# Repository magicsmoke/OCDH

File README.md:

View this project on [CADLAB.io](https://cadlab.io/project/25315). 

# OCDH
Open Source Diesel Heater

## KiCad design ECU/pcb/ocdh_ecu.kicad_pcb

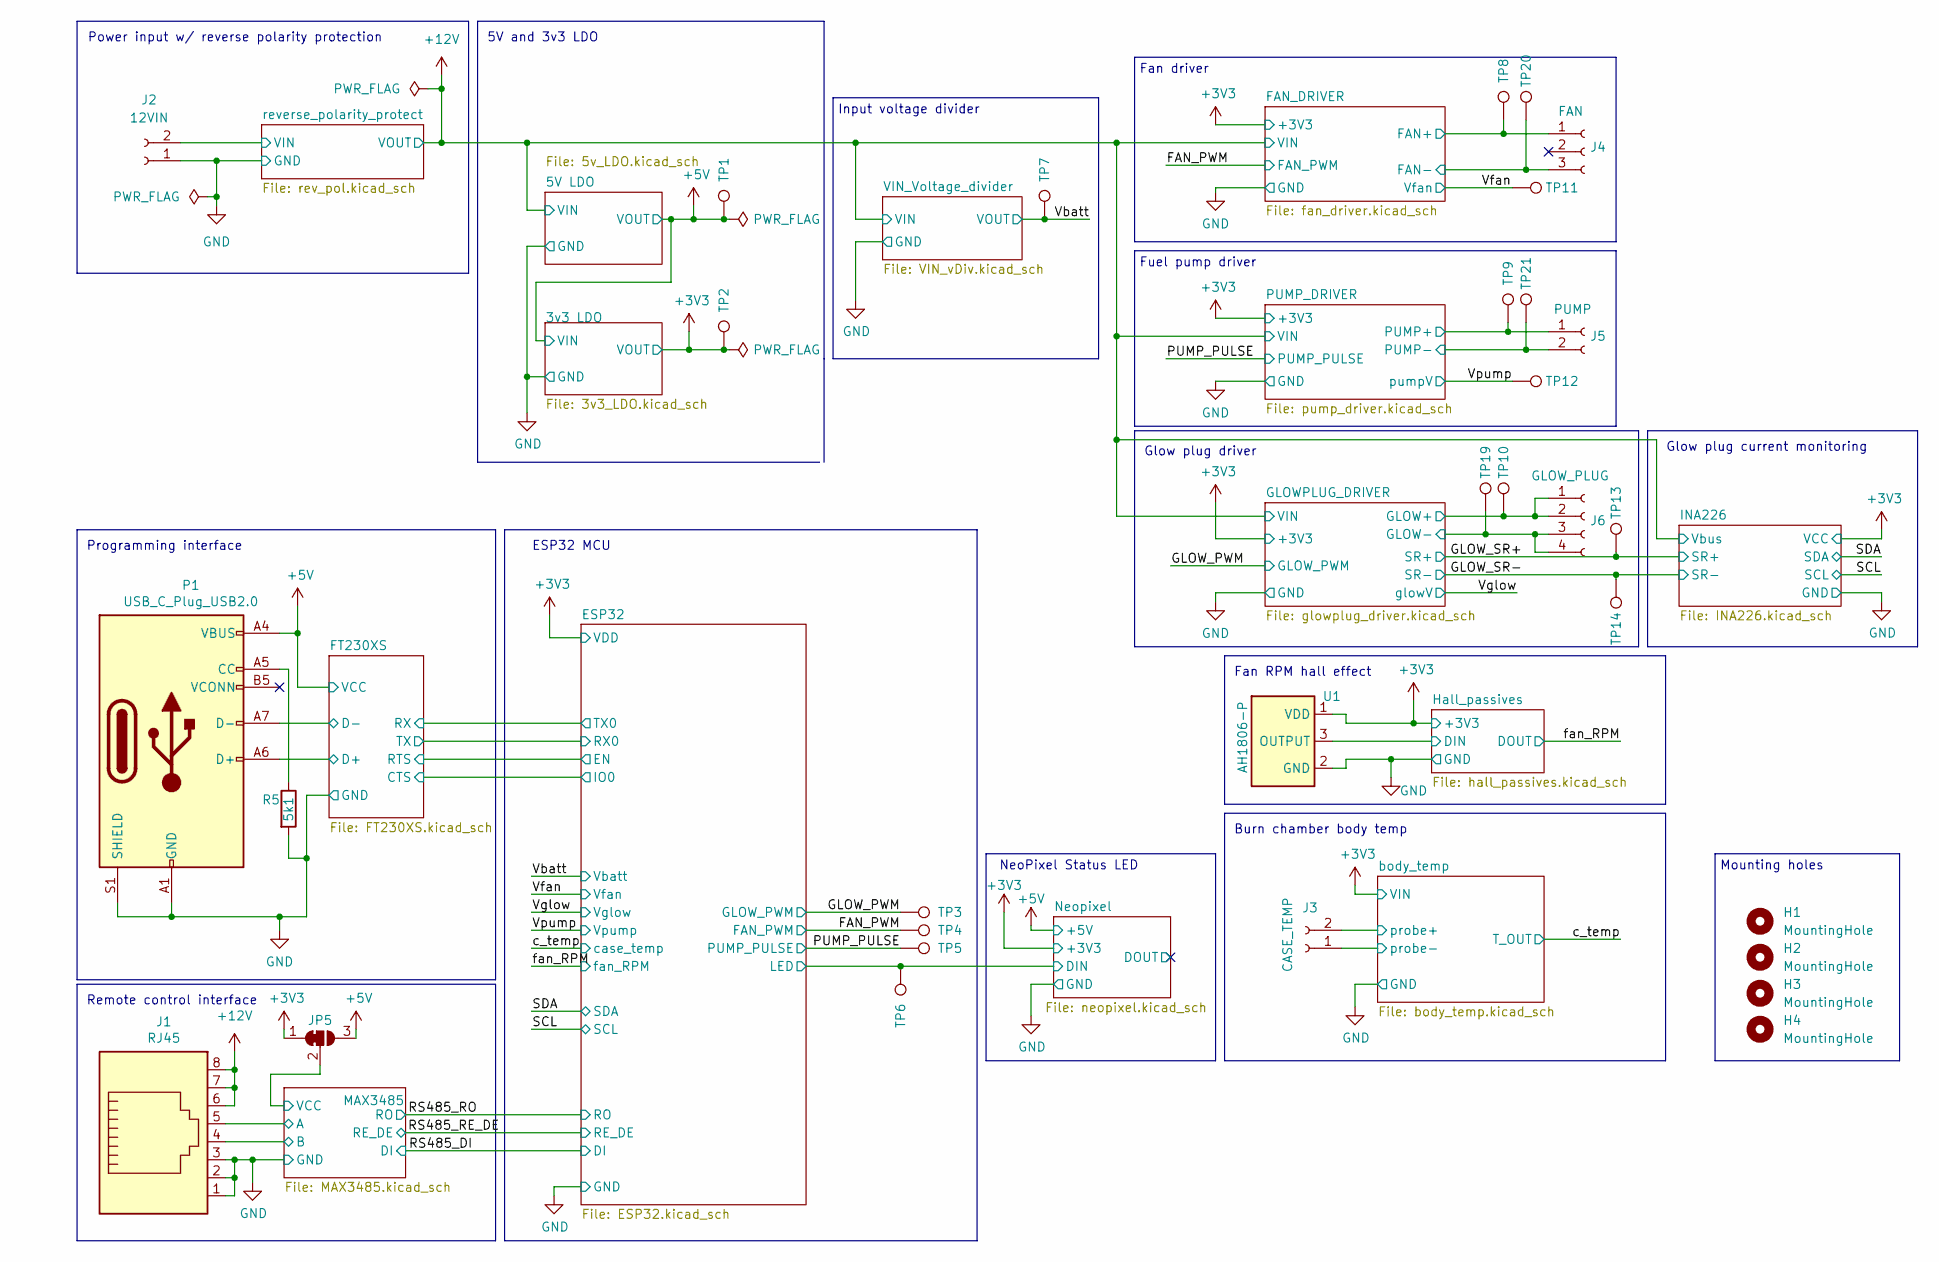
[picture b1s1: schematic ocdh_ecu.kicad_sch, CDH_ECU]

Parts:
H1, H2, H3, H4: MountingHole; MountingHole_3mm
J1: RJ45; RJ45_Amphenol_54602-x08_Horizontal
J2: 12VIN; SolderWire-1.5sqmm_1x02_P6mm_D1.7mm_OD3mm
J3: CASE_TEMP; SolderWire-1sqmm_1x02_P5.4mm_D1.4mm_OD2.7mm
J4: FAN; SolderWire-1sqmm_1x02_P5.4mm_D1.4mm_OD2.7mm
J5: PUMP; SolderWire-1sqmm_1x02_P5.4mm_D1.4mm_OD2.7mm
J6: GLOW_PLUG; SolderWire-1sqmm_1x02_P5.4mm_D1.4mm_OD2.7mm
JP5: RS485 PWR; SolderJumper-3_P1.3mm_Bridged12_RoundedPad1.0x1.5mm
P1: USB_C_Plug_USB2.0; GCT_USB4105-GF-A
R5: 5k1; R_0805_2012Metric
TP1, TP2, TP3, TP4, TP5, TP6, TP7, TP8, TP9, TP10, TP11, TP12, TP13, TP14, TP19, TP20, TP21: TestPoint; TestPoint_Pad_D1.5mm
U1: AH1806-P; TO265P160X410X495-3P

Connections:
+3V3: JP5.1 (A), TP2.1, U1.1 (VDD); also elsewhere on the board
+5V: JP5.3 (B), P1.A4 (VBUS), P1.A9 (VBUS), P1.B4 (VBUS), P1.B9 (VBUS), TP1.1; also elsewhere on the board
+12V: J1.6, J1.7, J1.8, J6.1, J6.2, TP10.1; also elsewhere on the board
/FAN_DRIVER/FAN+: J4.1, TP8.1; also elsewhere on the board
/FAN_DRIVER/FAN-: J4.3, TP20.1; also elsewhere on the board
/FAN_PWM: TP4.1; also elsewhere on the board
/FT230XS/D+: P1.A6 (D+), P1.B6 (D+); also elsewhere on the board
/FT230XS/D-: P1.A7 (D-), P1.B7 (D-); also elsewhere on the board
/GLOWPLUG_DRIVER/GLOW-: J6.3, J6.4, TP19.1; also elsewhere on the board
/GLOW_PWM: TP3.1; also elsewhere on the board
/GLOW_SR+: TP13.1; also elsewhere on the board
/GLOW_SR-: TP14.1; also elsewhere on the board
/Hall_passives/DIN: U1.3 (OUTPUT); also elsewhere on the board
/MAX3485/A: J1.5; also elsewhere on the board
/MAX3485/B: J1.4; also elsewhere on the board
/MAX3485/VCC: JP5.2 (C); also elsewhere on the board
/PUMP_DRIVER/PUMP+: J5.1, TP9.1; also elsewhere on the board
/PUMP_DRIVER/PUMP-: J5.2, TP21.1; also elsewhere on the board
/PUMP_PULSE: TP5.1; also elsewhere on the board
/Vbatt: TP7.1; also elsewhere on the board
/Vfan: TP11.1; also elsewhere on the board
/Vpump: TP12.1; also elsewhere on the board
/body_temp/probe+: J3.2; also elsewhere on the board
/body_temp/probe-: J3.1; also elsewhere on the board
/reverse_polarity_protect/VIN: J2.2; also elsewhere on the board
GND: J1.1, J1.2, J1.3, J2.1, P1.A1 (GND), P1.A12 (GND), P1.B1 (GND), P1.B12 (GND), P1.S1 (SHIELD), R5.2, U1.2 (GND); also elsewhere on the board
unnamed: P1.A5 (CC), R5.1

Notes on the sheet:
NeoPixel Status LED
Burn chamber body temp
ESP32 MCU
Programming interface
Fuel pump driver
5V and 3v3 LDO
Fan RPM hall effect
Glow plug current monitoring
Power input w/ reverse polarity protection
Input voltage divider
Remote control interface
Mounting holes
Glow plug driver
Fan driver

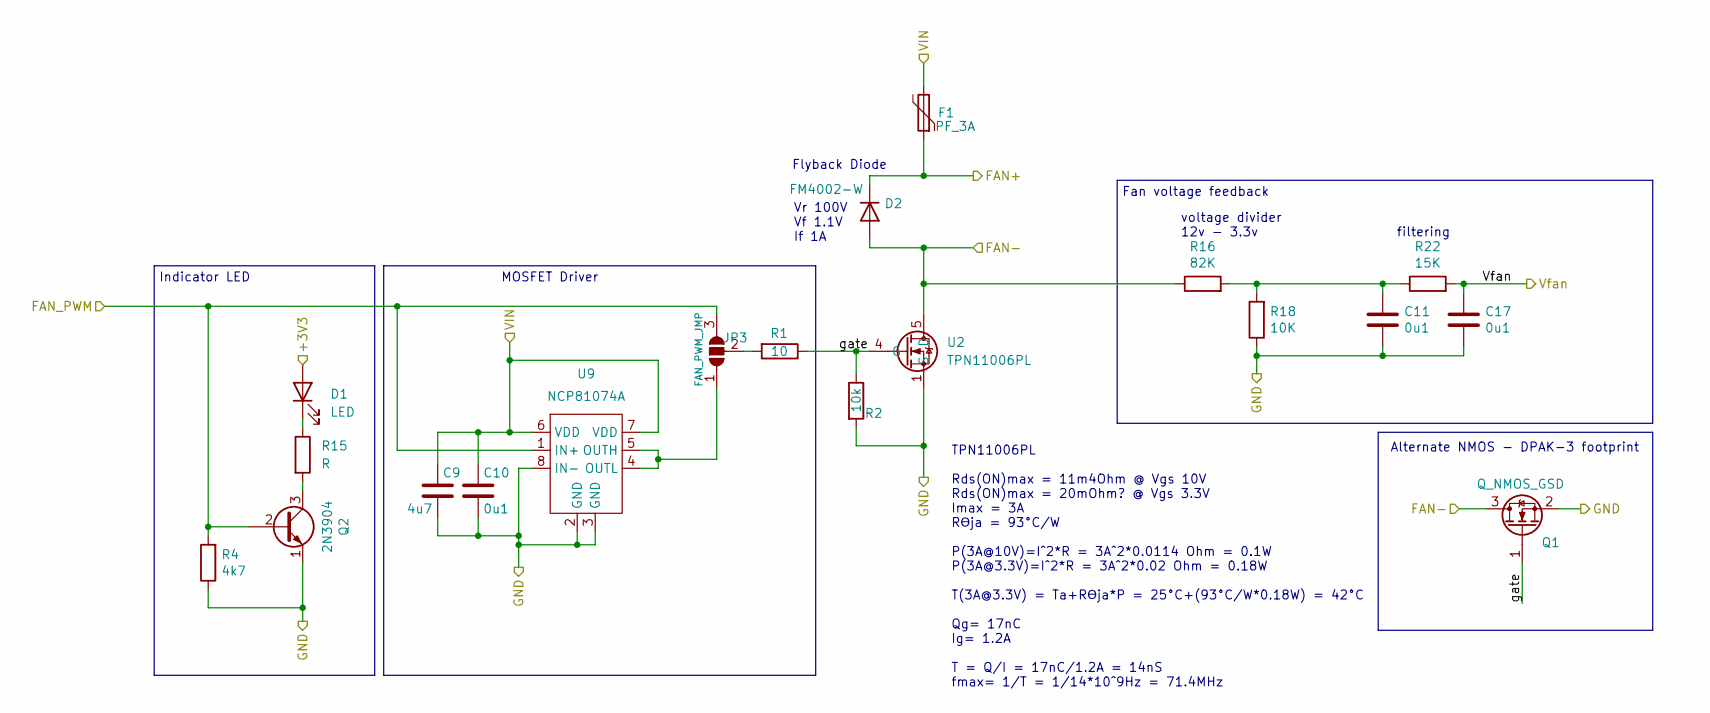
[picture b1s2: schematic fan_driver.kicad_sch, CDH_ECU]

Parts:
C9: 4u7; C_0805_2012Metric
C10, C11, C17: 0u1; C_0805_2012Metric
D1: LED; LEDC1608X80N
D2: FM4002-W; DIOM5025X231N
F1: PF_3A; Fuse_1812_4532Metric
JP3: FAN_PWM_JMP; SolderJumper-3_P1.3mm_Open_RoundedPad1.0x1.5mm_NumberLabels
Q1: Q_NMOS_GSD; TO-252-2
Q2: 2N3904; SOT-23
R1: 10; R_0805_2012Metric
R2: 10k; R_0805_2012Metric
R4: 4k7; R_0805_2012Metric
R15: R; R_0805_2012Metric
R16: 82K; R_0805_2012Metric
R18: 10K; R_0805_2012Metric
R22: 15K; R_0805_2012Metric
U2: TPN11006PL; VSON-8_3.3x3.3mm_P0.65mm_NexFET
U9: NCP81074A; SOIC-8_3.9x4.9mm_P1.27mm

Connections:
+3V3: D1.2 (A); also elsewhere on the board
+12V: C9.1, C10.1, F1.2, U9.6 (VDD), U9.7 (VDD); also elsewhere on the board
/FAN_DRIVER/FAN+: D2.1 (K), F1.1; also elsewhere on the board
/FAN_DRIVER/FAN-: D2.2 (A), Q1.3 (D), R16.1, U2.5 (D); also elsewhere on the board
/FAN_DRIVER/gate: Q1.1 (G), R1.1, R2.1, U2.4 (G)
/FAN_PWM: JP3.3 (B), Q2.2 (B), R4.2, U9.1 (IN+); also elsewhere on the board
/Vfan: C17.1, R22.2; also elsewhere on the board
GND: C9.2, C10.2, C11.2, C17.2, Q1.2 (S), Q2.1 (E), R2.2, R4.1, R18.1, U2.1 (S), U2.2 (S), U2.3 (S), U9.2 (GND), U9.3 (GND), U9.8 (IN-); also elsewhere on the board
unnamed: C11.1, R16.2, R18.2, R22.1
unnamed: D1.1 (K), R15.1
unnamed: JP3.1 (A), U9.4 (OUTL), U9.5 (OUTH)
unnamed: JP3.2 (C), R1.2
unnamed: Q2.3 (C), R15.2

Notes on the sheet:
filtering
TPN11006PL Rds(ON)max = 11m4Ohm @ Vgs 10V Rds(ON)max = 20mOhm? @ Vgs 3.3V Imax = 3A Rϴja = 93°C/W P(3A@10V)=I^2*R = 3A^2*0.0114 Ohm = 0.1W P(3A@3.3V)=I^2*R = 3A^2*0.02 Ohm = 0.18W T(3A@3.3V) = Ta+Rϴja*P = 25°C+(93°C/W*0.18W) = 42°C Qg= 17nC Ig= 1.2A T = Q/I = 17nC/1.2A = 14nS fmax= 1/T = 1/14*10^9H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
Indicator LED
Alternate NMOS - DPAK-3 footprint
Fan voltage feedback
Vr 100V Vf 1.1V If 1A
Flyback Diode
voltage divider 12v - 3.3v
MOSFET Driver

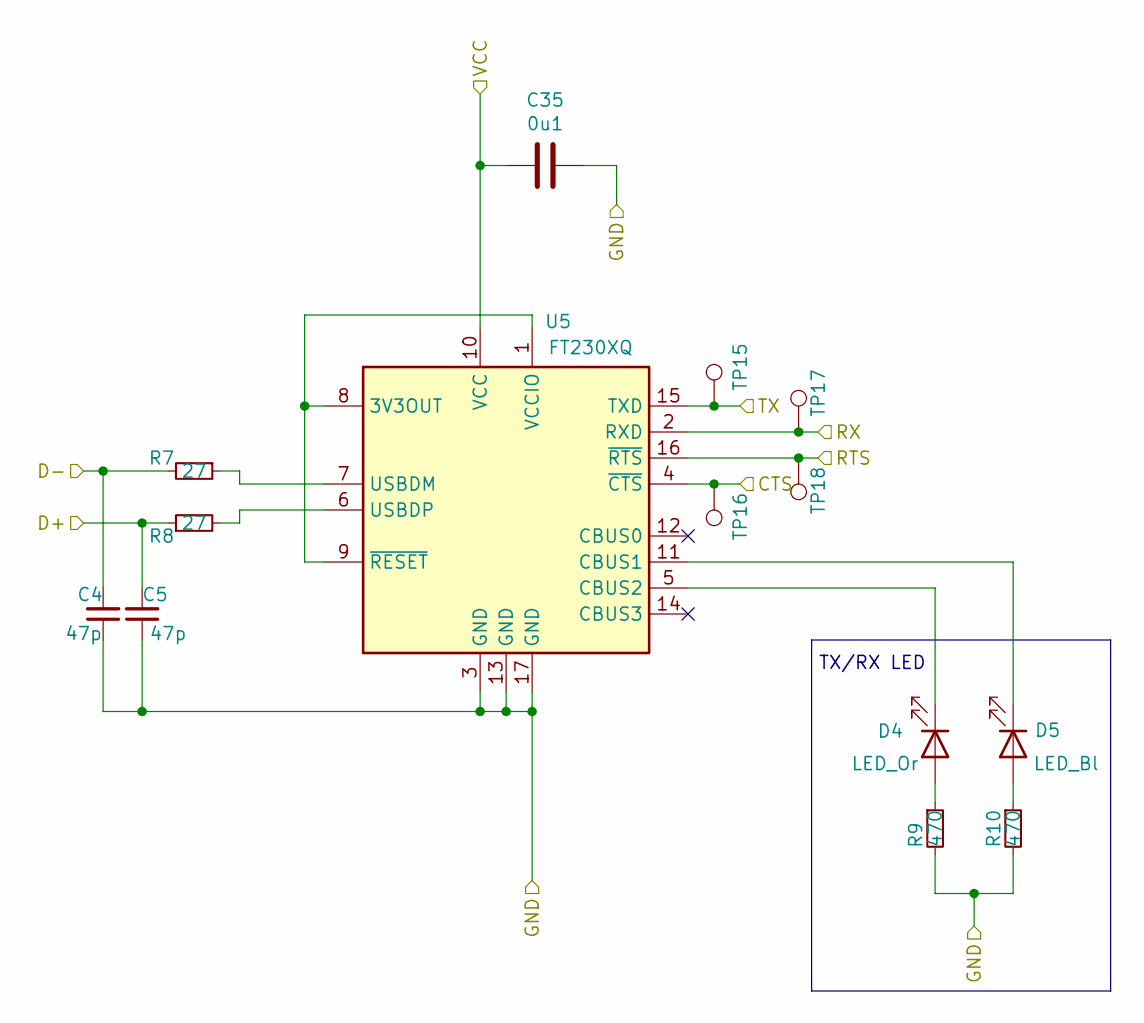
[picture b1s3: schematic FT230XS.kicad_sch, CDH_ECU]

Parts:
C4, C5: 47p; C_0805_2012Metric
C35: 0u1; C_0805_2012Metric
D4: LED_Or; LEDC1608X80N
D5: LED_Bl; LEDC1608X80N
R7, R8: 27; R_0805_2012Metric
R9, R10: 470; R_0805_2012Metric
TP15, TP16, TP17, TP18: TestPoint; TestPoint_Pad_D1.5mm
U5: FT230XQ; QFN-16-1EP_4x4mm_P0.65mm_EP2.1x2.1mm

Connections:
+5V: C35.2, U5.10 (VCC); also elsewhere on the board
/ESP32/EN: TP18.1, U5.16 (~RTS); also elsewhere on the board
/ESP32/IO0: TP16.1, U5.4 (~CTS); also elsewhere on the board
/ESP32/RX0: TP15.1, U5.15 (TXD); also elsewhere on the board
/ESP32/TX0: TP17.1, U5.2 (RXD); also elsewhere on the board
/FT230XS/D+: C5.2, R8.1; also elsewhere on the board
/FT230XS/D-: C4.2, R7.2; also elsewhere on the board
GND: C4.1, C5.1, C35.1, R9.2, R10.2, U5.3 (GND), U5.13 (GND), U5.17 (GND); also elsewhere on the board
unnamed: D4.1 (K), U5.5 (CBUS2)
unnamed: D4.2 (A), R9.1
unnamed: D5.1 (K), U5.11 (CBUS1)
unnamed: D5.2 (A), R10.1
unnamed: R7.1, U5.7 (USBDM)
unnamed: R8.2, U5.6 (USBDP)
unnamed: U5.1 (VCCIO), U5.8 (3V3OUT), U5.9 (~RESET)

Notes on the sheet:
TX/RX LED

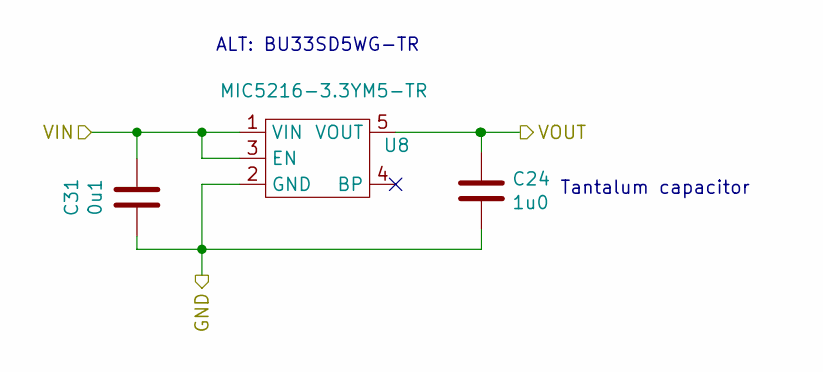
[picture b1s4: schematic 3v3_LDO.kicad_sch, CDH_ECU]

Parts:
C24: 1u0; C_0805_2012Metric
C31: 0u1; C_0805_2012Metric
U8: MIC5216-3.3YM5-TR; SOT-23-5

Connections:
+3V3: C24.1, U8.5 (VOUT); also elsewhere on the board
+5V: C31.1, U8.1 (VIN), U8.3 (EN); also elsewhere on the board
GND: C24.2, C31.2, U8.2 (GND); also elsewhere on the board

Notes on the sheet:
Tantalum capacitor
ALT: BU33SD5WG-TR

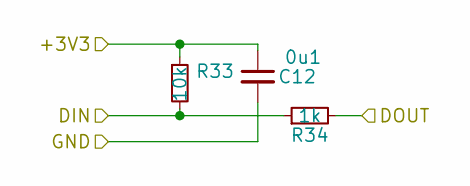
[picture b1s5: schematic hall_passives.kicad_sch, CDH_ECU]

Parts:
C12: 0u1; C_0805_2012Metric
R33: 10k; R_0805_2012Metric
R34: 1k; R_0805_2012Metric

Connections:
+3V3: C12.1, R33.1; also elsewhere on the board
/Hall_passives/DIN: R33.2, R34.1; also elsewhere on the board
/fan_RPM: R34.2; also elsewhere on the board
GND: C12.2; also elsewhere on the board

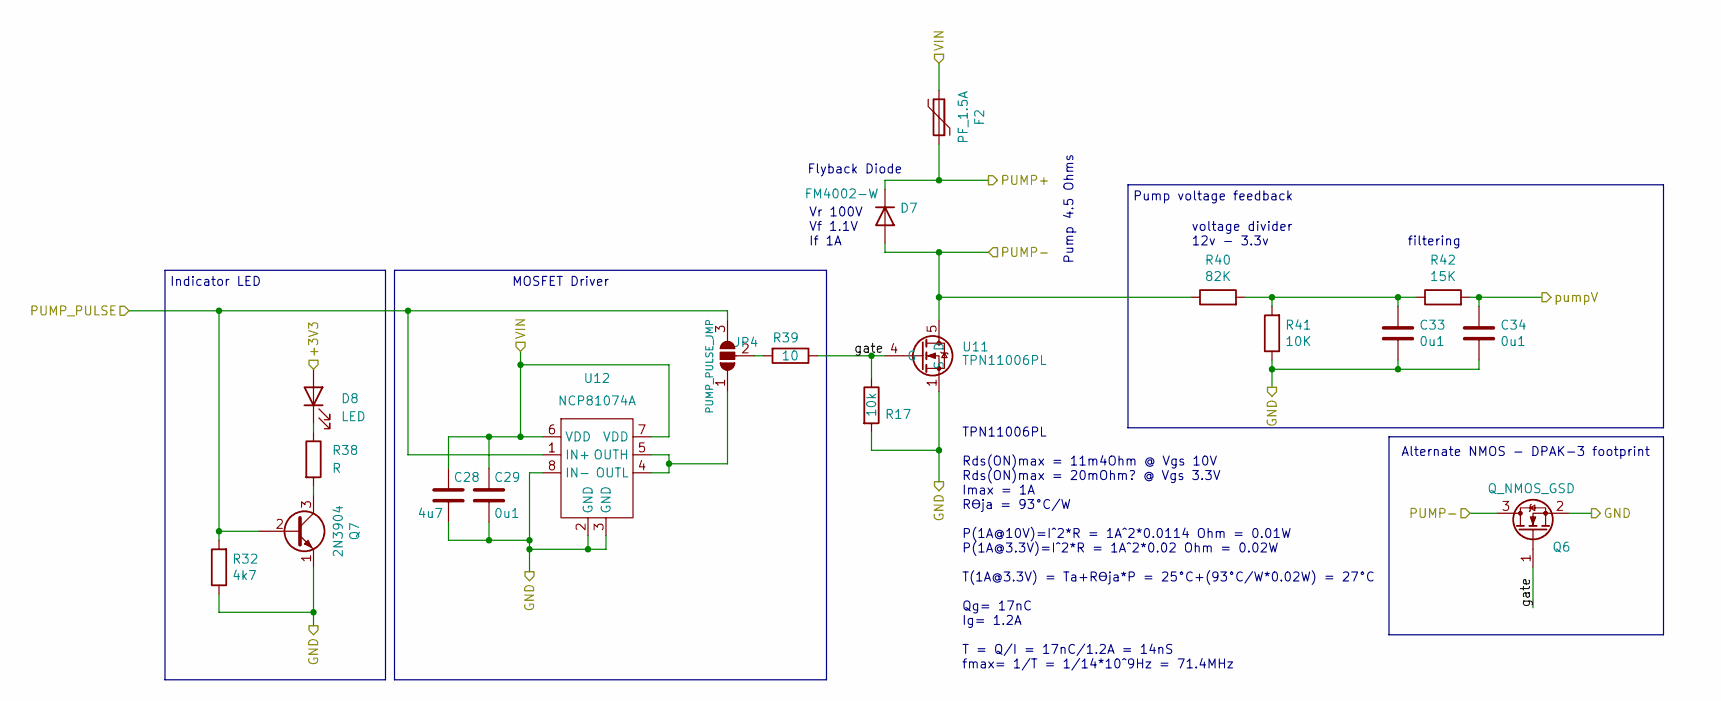
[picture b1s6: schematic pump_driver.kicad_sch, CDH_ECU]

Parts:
C28: 4u7; C_0805_2012Metric
C29, C33, C34: 0u1; C_0805_2012Metric
D7: FM4002-W; DIOM5025X231N
D8: LED; LEDC1608X80N
F2: PF_1.5A; FUSC5141X160N
JP4: PUMP_PULSE_JMP; SolderJumper-3_P1.3mm_Open_RoundedPad1.0x1.5mm_NumberLabels
Q6: Q_NMOS_GSD; TO-252-2
Q7: 2N3904; SOT-23
R17: 10k; R_0805_2012Metric
R32: 4k7; R_0805_2012Metric
R38: R; R_0805_2012Metric
R39: 10; R_0805_2012Metric
R40: 82K; R_0805_2012Metric
R41: 10K; R_0805_2012Metric
R42: 15K; R_0805_2012Metric
U11: TPN11006PL; VSON-8_3.3x3.3mm_P0.65mm_NexFET
U12: NCP81074A; SOIC-8_3.9x4.9mm_P1.27mm

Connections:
+3V3: D8.2 (A); also elsewhere on the board
+12V: C28.1, C29.1, F2.2, U12.6 (VDD), U12.7 (VDD); also elsewhere on the board
/PUMP_DRIVER/PUMP+: D7.1 (K), F2.1; also elsewhere on the board
/PUMP_DRIVER/PUMP-: D7.2 (A), Q6.3 (D), R40.1, U11.5 (D); also elsewhere on the board
/PUMP_DRIVER/gate: Q6.1 (G), R17.1, R39.1, U11.4 (G)
/PUMP_PULSE: JP4.3 (B), Q7.2 (B), R32.2, U12.1 (IN+); also elsewhere on the board
/Vpump: C34.1, R42.2; also elsewhere on the board
GND: C28.2, C29.2, C33.2, C34.2, Q6.2 (S), Q7.1 (E), R17.2, R32.1, R41.1, U11.1 (S), U11.2 (S), U11.3 (S), U12.2 (GND), U12.3 (GND), U12.8 (IN-); also elsewhere on the board
unnamed: C33.1, R40.2, R41.2, R42.1
unnamed: D8.1 (K), R38.1
unnamed: JP4.1 (A), U12.4 (OUTL), U12.5 (OUTH)
unnamed: JP4.2 (C), R39.2
unnamed: Q7.3 (C), R38.2

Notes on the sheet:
Flyback Diode
Vr 100V Vf 1.1V If 1A
Pump 4.5 Ohms
MOSFET Driver
filtering
voltage divider 12v - 3.3v
TPN11006PL Rds(ON)max = 11m4Ohm @ Vgs 10V Rds(ON)max = 20mOhm? @ Vgs 3.3V Imax = 1A Rϴja = 93°C/W P(1A@10V)=I^2*R = 1A^2*0.0114 Ohm = 0.01W P(1A@3.3V)=I^2*R = 1A^2*0.02 Ohm = 0.02W T(1A@3.3V) = Ta+Rϴja*P = 25°C+(93°C/W*0.02W) = 27°C Qg= 17nC Ig= 1.2A T = Q/I = 17nC/1.2A = 14nS fmax= 1/T = 1/14*10^9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
Indicator LED
Alternate NMOS - DPAK-3 footprint
Pump voltage feedback

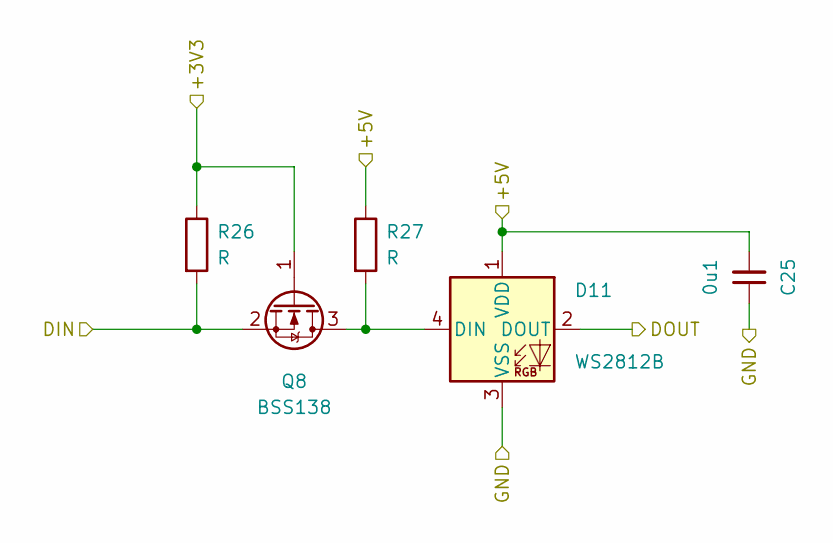
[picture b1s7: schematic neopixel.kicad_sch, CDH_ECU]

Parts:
C25: 0u1; C_0805_2012Metric
D11: WS2812B; LED_WS2812B_PLCC4_5.0x5.0mm_P3.2mm
Q8: BSS138; SOT-23
R26, R27: R; R_0805_2012Metric

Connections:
+3V3: Q8.1 (G), R26.1; also elsewhere on the board
+5V: C25.2, D11.1 (VDD), R27.1; also elsewhere on the board
/ESP32/LED: Q8.2 (S), R26.2; also elsewhere on the board
/Neopixel/DOUT: D11.2 (DOUT)
GND: C25.1, D11.3 (VSS); also elsewhere on the board
unnamed: D11.4 (DIN), Q8.3 (D), R27.2

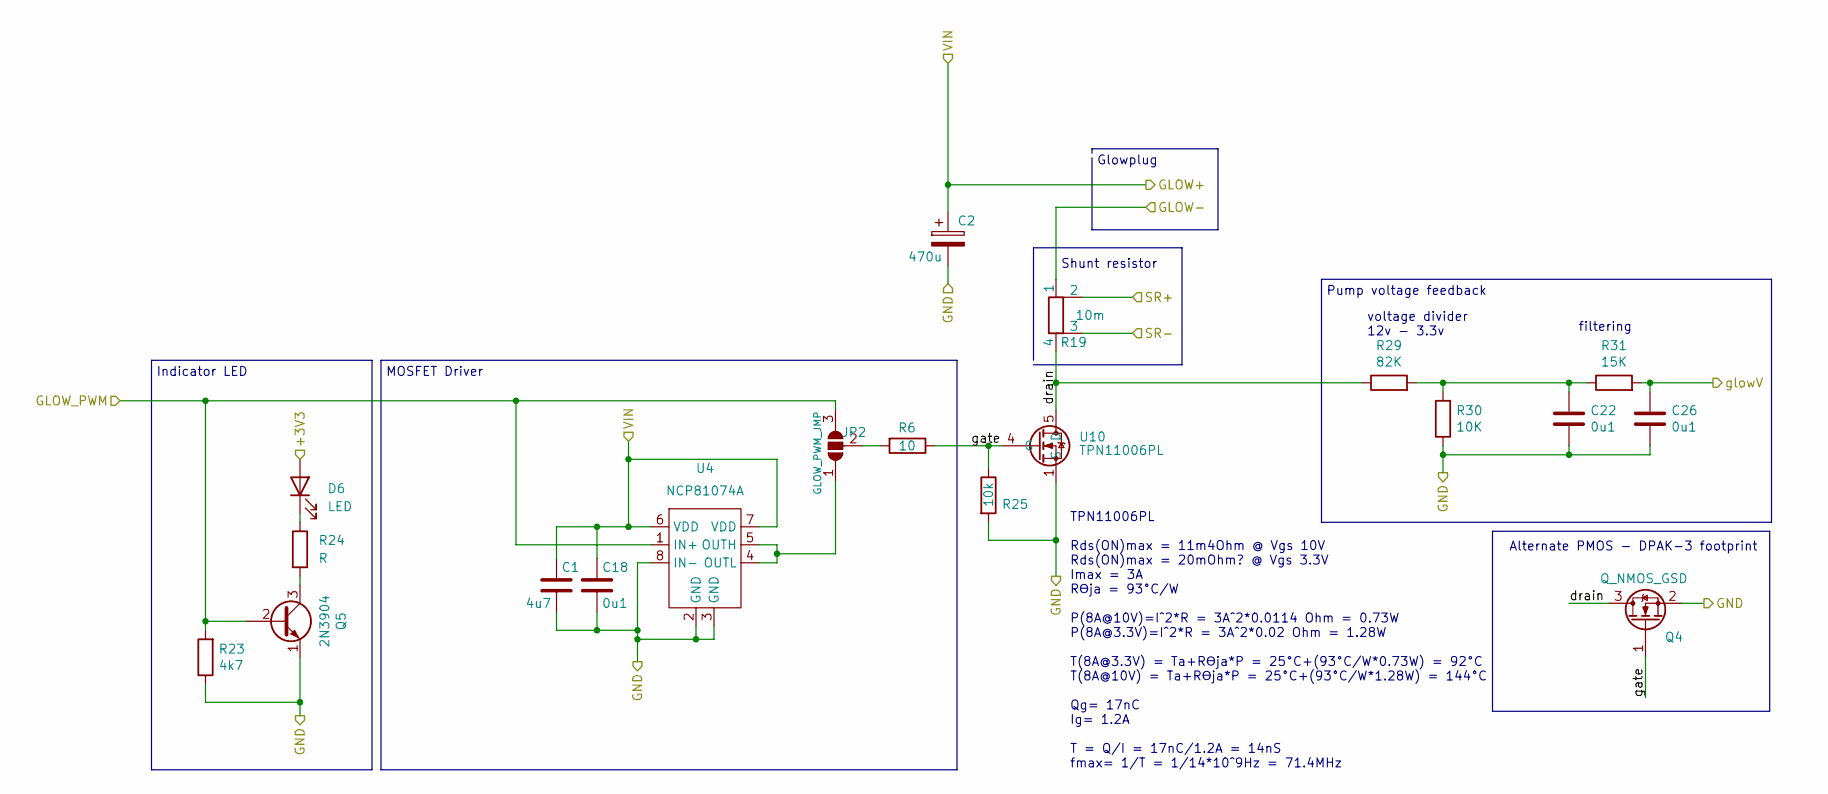
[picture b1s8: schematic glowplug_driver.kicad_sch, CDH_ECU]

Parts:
C1: 4u7; C_0805_2012Metric
C2: 470u; CP_Radial_D10.0mm_P5.00mm
C18, C22, C26: 0u1; C_0805_2012Metric
D6: LED; LEDC1608X80N
JP2: GLOW_PWM_JMP; SolderJumper-3_P1.3mm_Open_RoundedPad1.0x1.5mm_NumberLabels
Q4: Q_NMOS_GSD; TO-252-2
Q5: 2N3904; SOT-23
R6: 10; R_0805_2012Metric
R19: 10m; R_Shunt_Vishay_WSK2512_6332Metric_T1.19mm
R23: 4k7; R_0805_2012Metric
R24: R; R_0805_2012Metric
R25: 10k; R_0805_2012Metric
R29: 82K; R_0805_2012Metric
R30: 10K; R_0805_2012Metric
R31: 15K; R_0805_2012Metric
U4: NCP81074A; SOIC-8_3.9x4.9mm_P1.27mm
U10: TPN11006PL; VSON-8_3.3x3.3mm_P0.65mm_NexFET

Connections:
+3V3: D6.2 (A); also elsewhere on the board
+12V: C1.1, C2.1, C18.1, U4.6 (VDD), U4.7 (VDD); also elsewhere on the board
/GLOWPLUG_DRIVER/GLOW-: R19.1; also elsewhere on the board
/GLOWPLUG_DRIVER/drain: Q4.3 (D), R19.4, R29.1, U10.5 (D)
/GLOWPLUG_DRIVER/gate: Q4.1 (G), R6.1, R25.1, U10.4 (G)
/GLOW_PWM: JP2.3 (B), Q5.2 (B), R23.2, U4.1 (IN+); also elsewhere on the board
/GLOW_SR+: R19.2; also elsewhere on the board
/GLOW_SR-: R19.3; also elsewhere on the board
/Vglow: C26.1, R31.2; also elsewhere on the board
GND: C1.2, C2.2, C18.2, C22.2, C26.2, Q4.2 (S), Q5.1 (E), R23.1, R25.2, R30.1, U4.2 (GND), U4.3 (GND), U4.8 (IN-), U10.1 (S), U10.2 (S), U10.3 (S); also elsewhere on the board
unnamed: C22.1, R29.2, R30.2, R31.1
unnamed: D6.1 (K), R24.1
unnamed: JP2.1 (A), U4.4 (OUTL), U4.5 (OUTH)
unnamed: JP2.2 (C), R6.2
unnamed: Q5.3 (C), R24.2

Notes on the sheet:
Alternate PMOS - DPAK-3 footprint
Shunt resistor
Pump voltage feedback
voltage divider 12v - 3.3v
MOSFET Driver
Glowplug
TPN11006PL Rds(ON)max = 11m4Ohm @ Vgs 10V Rds(ON)max = 20mOhm? @ Vgs 3.3V Imax = 3A Rϴja = 93°C/W P(8A@10V)=I^2*R = 3A^2*0.0114 Ohm = 0.73W P(8A@3.3V)=I^2*R = 3A^2*0.02 Ohm = 1.28W T(8A@3.3V) = Ta+Rϴja*P = 25°C+(93°C/W*0.73W) = 92°C T(8A@10V) = Ta+Rϴja*P = 25°C+(93°C/W*1.28W) = 144°C Qg= 17nC Ig= 1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
Indicator LED
filtering

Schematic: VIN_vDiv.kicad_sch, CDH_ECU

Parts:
C36, C37: 0u1; C_0805_2012Metric
R43: 82K; R_0805_2012Metric
R44: 10K; R_0805_2012Metric
R45: 15K; R_0805_2012Metric

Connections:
+12V: R43.1; also elsewhere on the board
/Vbatt: C37.1, R45.2; also elsewhere on the board
GND: C36.2, C37.2, R44.1; also elsewhere on the board
unnamed: C36.1, R43.2, R44.2, R45.1

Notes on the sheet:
filtering
Voltage divider calculation Vin = Vout 14V = 1.47V 12V = 1.26V 10V = 1.05V ~~~~~~~~~~~~~~~~~~~~~~~~~~~~~~~~~~~~~~~~~~ ESP32 ADC Attenuation ADC_ATTEN_DB_6 150 mV ~ 1750 mV
voltage divider 12v - 3.3v

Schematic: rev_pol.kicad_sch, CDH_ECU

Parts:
D3: BZX884B10L; D_0402_1005Metric
Q3: SiSS27DN; Vishay_PowerPAK_1212-8_Single
Q11: ALT_PMOS_DPAK3; TO-252-2
R3: 100K; R_0805_2012Metric

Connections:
+12V: D3.1 (K), Q3.1 (S), Q3.2 (S), Q3.3 (S), Q11.2 (S); also elsewhere on the board
/reverse_polarity_protect/VIN: Q3.5 (D), Q11.3 (D); also elsewhere on the board
/reverse_polarity_protect/gate: D3.2 (A), Q3.4 (G), Q11.1 (G), R3.1
GND: R3.2; also elsewhere on the board

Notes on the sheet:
SiSS27DN Rds(ON)= 5m6Ohm @ Vgs -10V Rϴja = 26°C/W P(16A)=I^2*R = 16A^2*0.0056 Ohm = 1.4W (nice) T = Ta+Rϴja*P = 25°C+(26°C/W*1.4W) = 62°C
ALT:SISS63DN
10V
Alternate PMOS - DPAK-3 footprint

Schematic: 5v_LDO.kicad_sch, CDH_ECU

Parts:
C16, C23: 1u0; C_0805_2012Metric
C30: 0u1; C_0805_2012Metric
U7: MIC5239-5.0YS-TR; SOT-223

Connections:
+5V: C23.1, U7.3 (OUT); also elsewhere on the board
+12V: C16.1, C30.1, U7.1 (IN); also elsewhere on the board
GND: C16.2, C23.2, C30.2, U7.2 (GND), U7.4 (GND); also elsewhere on the board

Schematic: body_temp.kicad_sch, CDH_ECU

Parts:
C13, C14, C15: 100n; C_0805_2012Metric
R35: 390; R_0805_2012Metric
R36: 49k; R_0805_2012Metric
R37: 15k; R_0805_2012Metric

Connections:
+3V3: R35.1; also elsewhere on the board
/body_temp/probe+: C13.1, R35.2; also elsewhere on the board
/body_temp/probe-: C14.1, R36.1, R37.2; also elsewhere on the board
/c_temp: C15.1, R37.1; also elsewhere on the board
GND: C13.2, C14.2, C15.2, R36.2; also elsewhere on the board

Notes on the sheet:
https://www.bapihvac.com/wp-content/uploads/2010/11/Thermistor_47K.pdf
47k thermistor

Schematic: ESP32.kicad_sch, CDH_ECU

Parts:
C6, C8: 0u1; C_0805_2012Metric
C7: 22u; C_0805_2012Metric
JP1: OTA_EN; PinSocket_1x02_P2.54mm_Vertical
R11: 10k; R_0805_2012Metric
R12, R13, R14: 4k7; R_0805_2012Metric
SW1: Reset; SW_SPST_PTS645
SW2: Boot/Flash; PinHeader_1x02_P1.27mm_Vertical
U6: ESP32-WROOM-32

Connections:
+3V3: C6.2, C7.2, R11.1, R13.2, R14.2, U6.2 (VDD); also elsewhere on the board
/ESP32/EN: C8.1, R11.2, SW1.2, U6.3 (EN); also elsewhere on the board
/ESP32/IO0: SW2.1, U6.25 (IO0); also elsewhere on the board
/ESP32/LED: R12.1; also elsewhere on the board
/ESP32/RX0: U6.34 (RXD0/IO3); also elsewhere on the board
/ESP32/TX0: U6.35 (TXD0/IO1); also elsewhere on the board
/FAN_PWM: U6.31 (IO19); also elsewhere on the board
/GLOW_PWM: U6.37 (IO23); also elsewhere on the board
/PUMP_PULSE: U6.30 (IO18); also elsewhere on the board
/RS485_DI: U6.12 (IO27); also elsewhere on the board
/RS485_RE_DE: U6.8 (IO32); also elsewhere on the board
/RS485_RO: U6.11 (IO26); also elsewhere on the board
/SCL: R13.1, U6.36 (IO22); also elsewhere on the board
/SDA: R14.1, U6.33 (IO21); also elsewhere on the board
/Vbatt: U6.26 (IO4); also elsewhere on the board
/Vfan: U6.14 (IO12); also elsewhere on the board
/Vglow: U6.29 (IO5); also elsewhere on the board
/Vpump: U6.13 (IO14); also elsewhere on the board
/c_temp: U6.27 (IO16); also elsewhere on the board
/fan_RPM: U6.28 (IO17); also elsewhere on the board
GND: C6.1, C7.1, C8.2, JP1.2 (B), SW1.1, SW2.2, U6.1 (GND), U6.15 (GND), U6.38 (GND), U6.39 (GND); also elsewhere on the board
unnamed: JP1.1 (A), U6.16 (IO13)
unnamed: R12.2, U6.23 (IO15)

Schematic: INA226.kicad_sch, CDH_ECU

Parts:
C3, C27: 0u1; C_0805_2012Metric
J7: Pad; TestPoint_Pad_D1.5mm
R20, R21: 10; R_0805_2012Metric
U3: INA226; VSSOP-10_3x3mm_P0.5mm

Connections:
+3V3: C27.2, U3.6 (VS); also elsewhere on the board
+12V: U3.8 (Vbus); also elsewhere on the board
/GLOW_SR+: R20.2; also elsewhere on the board
/GLOW_SR-: R21.2; also elsewhere on the board
/SCL: U3.5 (SCL); also elsewhere on the board
/SDA: U3.4 (SDA); also elsewhere on the board
GND: C27.1, U3.1 (A1), U3.2 (A0), U3.7 (GND); also elsewhere on the board
unnamed: C3.1, R21.1, U3.9 (Vin-)
unnamed: C3.2, R20.1, U3.10 (Vin+)
unnamed: J7.1, U3.3 (~Alert)

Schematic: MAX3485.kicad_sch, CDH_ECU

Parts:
C32: 0u1; C_0805_2012Metric
R55, R56, R58: 10k; R_0805_2012Metric
R59: 120; R_0805_2012Metric
R60, R61: 20k; R_0805_2012Metric
U14: MAX3485; SOIC-8_3.9x4.9mm_P1.27mm

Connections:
/MAX3485/A: R59.2, R60.2, U14.6 (A); also elsewhere on the board
/MAX3485/B: R59.1, R61.1, U14.7 (B); also elsewhere on the board
/MAX3485/VCC: C32.1, R55.1, R56.1, R58.1, R60.1, U14.8 (VCC); also elsewhere on the board
/RS485_DI: R58.2, U14.4 (DI); also elsewhere on the board
/RS485_RE_DE: R56.2, U14.2 (~RE), U14.3 (DE); also elsewhere on the board
/RS485_RO: R55.2, U14.1 (RO); also elsewhere on the board
GND: C32.2, R61.2, U14.5 (GND); also elsewhere on the board

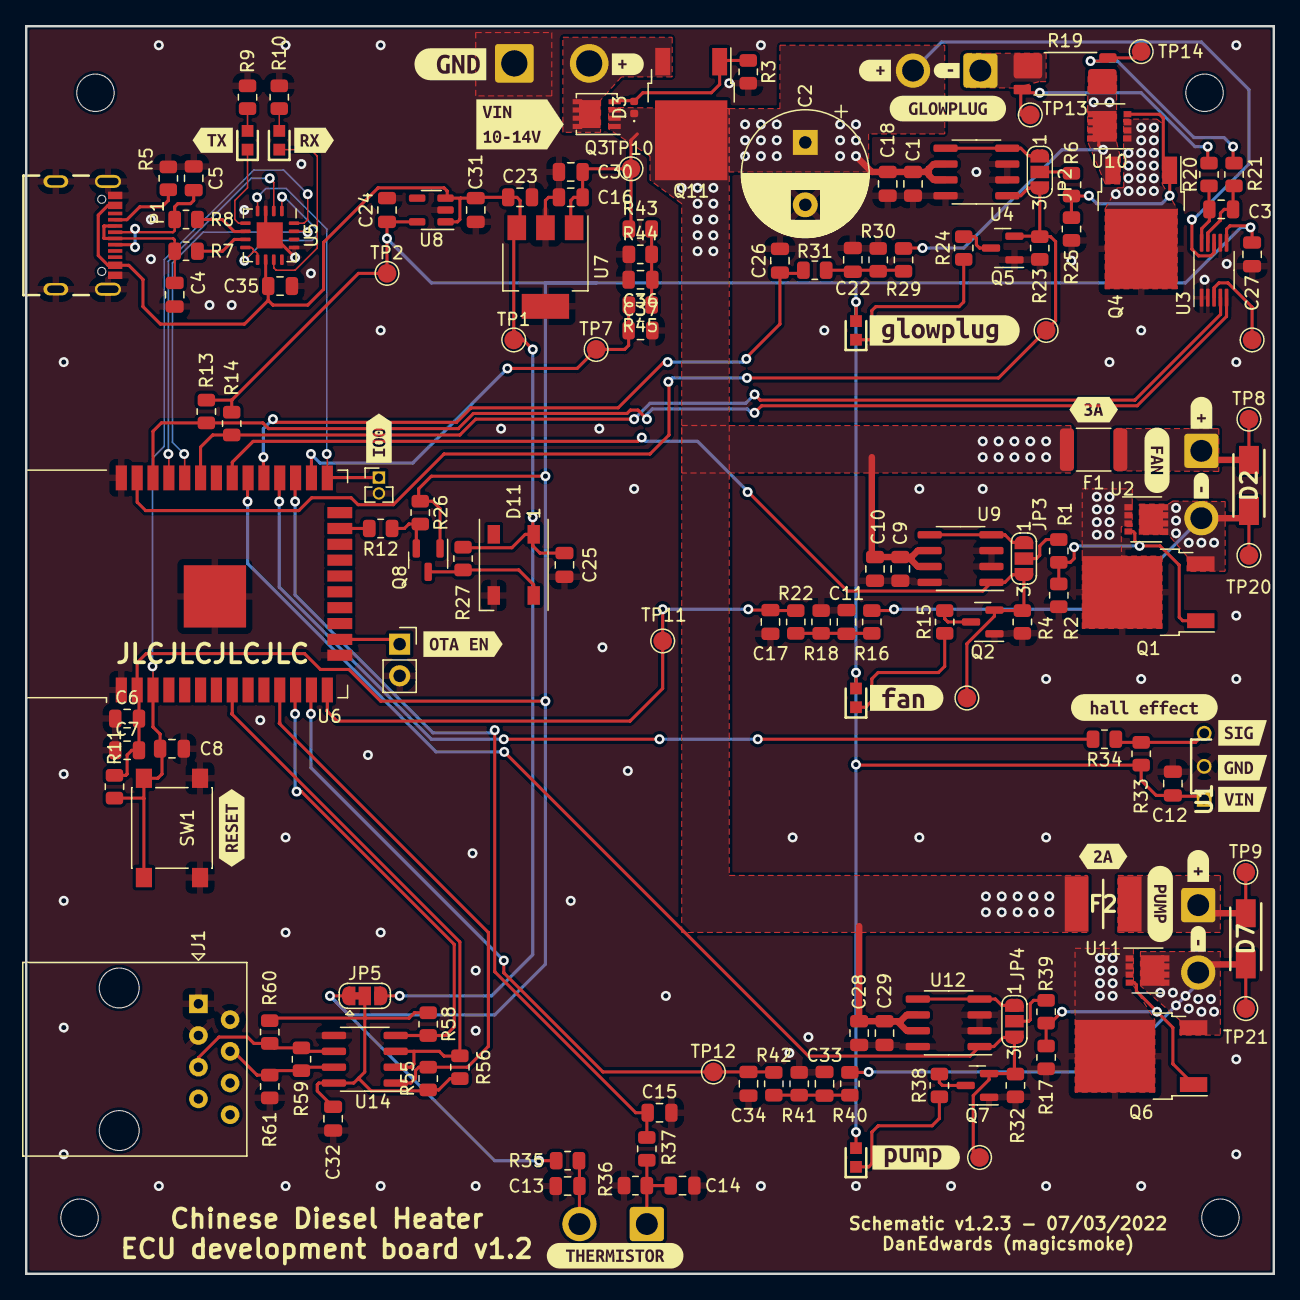
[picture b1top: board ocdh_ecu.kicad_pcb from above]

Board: 4 copper layers, 100.0 x 100.0 mm, 178 parts (0 on the bottom side), 74 nets.

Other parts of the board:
kibuzzard-6225E5A1: G***; kibuzzard-6225E5A1
kibuzzard-6225F900: G***; kibuzzard-6225F900
kibuzzard-62261A13: G***; kibuzzard-62261A13
kibuzzard-62261A48, kibuzzard-62261A48#2, kibuzzard-62261A48#3: G***; kibuzzard-62261A48
kibuzzard-62261B26: G***; kibuzzard-62261B26
kibuzzard-62261B32: G***; kibuzzard-62261B32
kibuzzard-62261E42: G***; kibuzzard-62261E42
kibuzzard-62261EA9: G***; kibuzzard-62261EA9
kibuzzard-62261EF2: G***; kibuzzard-62261EF2
kibuzzard-62261EFE: G***; kibuzzard-62261EFE
kibuzzard-62261F25: G***; kibuzzard-62261F25
kibuzzard-62261FB6: G***; kibuzzard-62261FB6
kibuzzard-622601F8: G***; kibuzzard-622601F8
kibuzzard-622618BB: G***; kibuzzard-622618BB
kibuzzard-622618D3: G***; kibuzzard-622618D3
kibuzzard-622619A2: G***; kibuzzard-622619A2
kibuzzard-622619E2: G***; kibuzzard-622619E2
kibuzzard-6226198A: G***; kibuzzard-6226198A
kibuzzard-62261823: G***; kibuzzard-62261823
kibuzzard-62261844, kibuzzard-62261844#2, kibuzzard-62261844#3, kibuzzard-62261844#4: G***; kibuzzard-62261844
kibuzzard-62261864: G***; kibuzzard-62261864
kibuzzard-62262057: G***; kibuzzard-62262057

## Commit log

2022-03-17 Initial commit schematic and board
    v1.2.3 schematic + v1.2
2022-03-17 Backlink to CADLAB.io has been added.
